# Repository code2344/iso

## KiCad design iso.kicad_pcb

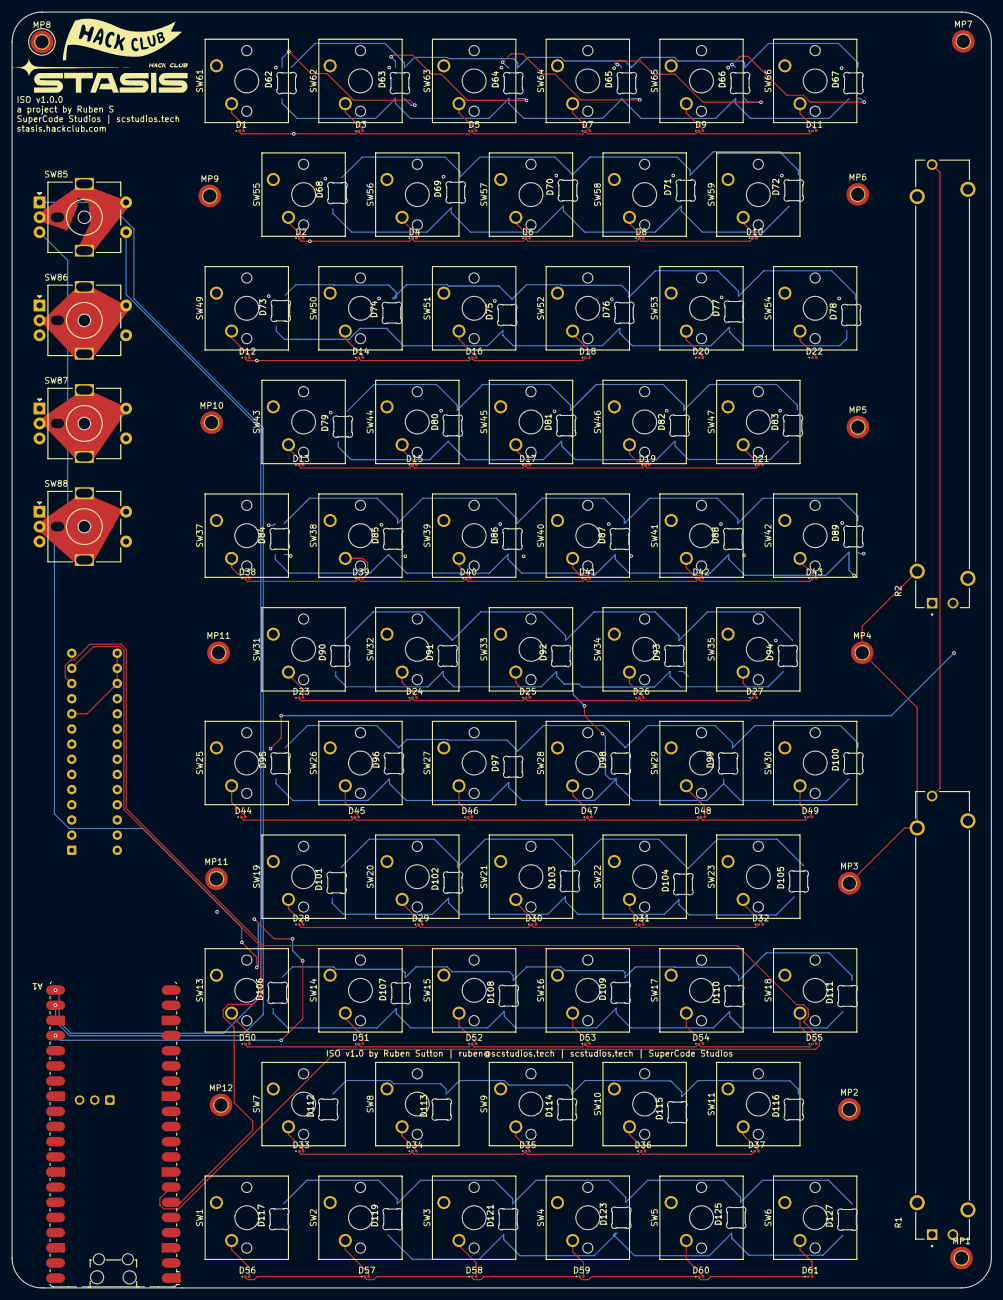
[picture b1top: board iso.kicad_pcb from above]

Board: 4 copper layers, 164.1 x 213.8 mm, 204 parts (1 on the bottom side), 158 nets.

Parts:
A1: RaspberryPi_Pico_W; RaspberryPi_Pico_W_SMD_HandSolder
D1, D2, D3, D4, D5, D6, D7, D8, D9, D10, D11, D12, D13, D14, D15, D16, D17, D18, D19, D20, D21, D22, D23, D24, D25, D26, D27, D28, D29, D30, D31, D32, D33, D34, D35, D36, D37, D38, D39, D40, D41, D42, D43, D44, D45, D46, D47, D48, D49, D50, D51, D52, D53, D54, D55, D56, D57, D58, D59, D60, D61: D_Small; D_0201_0603Metric
D62, D63, D64, D65, D66, D67, D68, D69, D70, D71, D72, D73, D74, D75, D76, D77, D78, D79, D80, D81, D82, D83, D84, D85, D86, D87, D88, D89, D90, D91, D92, D93, D94, D95, D96, D97, D98, D99, D100, D101, D102, D103, D104, D105, D106, D107, D108, D109, D110, D111, D112, D113, D114, D115, D116, D117, D119, D121, D123, D125, D127: SK6812; SK6812MINI-E_fixed
MP1, MP2, MP3, MP4, MP5, MP6, MP7, MP8, MP9, MP10, MP11, MP11#2, MP12: MountingHole_2.2mm_M2_DIN965_Pad_TopBottom
R1, R2: PTA6043-2015DPB103; TRIM_PTA6043-2015DPB103
SW1, SW2, SW3, SW4, SW5, SW6, SW7, SW8, SW9, SW10, SW11, SW13, SW14, SW15, SW16, SW17, SW18, SW19, SW20, SW21, SW22, SW23, SW25, SW26, SW27, SW28, SW29, SW30, SW31, SW32, SW33, SW34, SW35, SW37, SW38, SW39, SW40, SW41, SW42, SW43, SW44, SW45, SW46, SW47, SW49, SW50, SW51, SW52, SW53, SW54, SW55, SW56, SW57, SW58, SW59, SW61, SW62, SW63, SW64, SW65, SW66: SW_Push; SW_Cherry_MX_1.00u_PCB
SW85, SW86, SW87, SW88: RotaryEncoder_Switch_MP; RotaryEncoder_Alps_EC11E-Switch_Vertical_H20mm_MountingHoles
U1: MCP23017_SP; DIP-28_W7.62mm

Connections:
+3.3V: R1.3, R2.3
+5V: D62.3 (VDD), D63.3 (VDD), D64.3 (VDD), D65.3 (VDD), D66.3 (VDD), D67.3 (VDD), D68.3 (VDD), D69.3 (VDD), D70.3 (VDD), D71.3 (VDD), D72.3 (VDD), D73.3 (VDD), D74.3 (VDD), D75.3 (VDD), D76.3 (VDD), D77.3 (VDD), D78.3 (VDD), D79.3 (VDD), D80.3 (VDD), D81.3 (VDD), D82.3 (VDD), D83.3 (VDD), D84.3 (VDD), D85.3 (VDD), D86.3 (VDD), D87.3 (VDD), D88.3 (VDD), D89.3 (VDD), D90.3 (VDD), D91.3 (VDD), D92.3 (VDD), D93.3 (VDD), D94.3 (VDD), D95.3 (VDD), D96.3 (VDD), D97.3 (VDD), D98.3 (VDD), D99.3 (VDD), D100.3 (VDD), D101.3 (VDD), D102.3 (VDD), D103.3 (VDD), D104.3 (VDD), D105.3 (VDD), D106.3 (VDD), D107.3 (VDD), D108.3 (VDD), D109.3 (VDD), D110.3 (VDD), D111.3 (VDD), D112.3 (VDD), D113.3 (VDD), D114.3 (VDD), D115.3 (VDD), D116.3 (VDD), D117.3 (VDD), D119.3 (VDD), D121.3 (VDD), D123.3 (VDD), D125.3 (VDD), D127.3 (VDD)
/2A: A1.9 (GPIO6), SW86.A
/2S: A1.10 (GPIO7), SW86.S1
/3A: A1.11 (GPIO8), SW87.A
/3S: A1.12 (GPIO9), SW87.S1
/4A: A1.14 (GPIO10), SW88.A
/4S: A1.15 (GPIO11), SW88.S1
/ADC1: A1.32 (GPIO27_ADC1), R2.2
/ADC2: A1.34 (GPIO28_ADC2), R1.2
/LEDDIN: A1.16 (GPIO12), D62.2 (DIN)
/SCL: A1.7 (GPIO5), U1.12 (SCK)
/SDA: A1.6 (GPIO4), U1.13 (SDA)
/matrix/COL0: SW1.1, SW7.1, SW13.1, SW19.1, SW25.1, SW31.1, SW37.1, SW43.1, SW49.1, SW55.1, SW61.1, U1.5 (GPB4)
/matrix/COL1: SW2.1, SW8.1, SW14.1, SW20.1, SW26.1, SW32.1, SW38.1, SW44.1, SW50.1, SW56.1, SW62.1, U1.4 (GPB3)
/matrix/COL2: SW3.1, SW9.1, SW15.1, SW21.1, SW27.1, SW33.1, SW39.1, SW45.1, SW51.1, SW57.1, SW63.1, U1.3 (GPB2)
/matrix/COL3: SW4.1, SW10.1, SW16.1, SW22.1, SW28.1, SW34.1, SW40.1, SW46.1, SW52.1, SW58.1, SW64.1, U1.2 (GPB1)
/matrix/COL4: SW5.1, SW11.1, SW17.1, SW23.1, SW29.1, SW35.1, SW41.1, SW47.1, SW53.1, SW59.1, SW65.1, U1.1 (GPB0)
/matrix/COL5: A1.29 (GPIO22), SW6.1, SW18.1, SW30.1, SW42.1, SW54.1, SW66.1
/matrix/ROW0: D1.1 (K), D3.1 (K), D5.1 (K), D7.1 (K), D9.1 (K), D11.1 (K), U1.6 (GPB5)
/matrix/ROW1: D2.1 (K), D4.1 (K), D6.1 (K), D8.1 (K), D10.1 (K), U1.7 (GPB6)
/matrix/ROW2: D12.1 (K), D14.1 (K), D16.1 (K), D18.1 (K), D20.1 (K), D22.1 (K), U1.8 (GPB7)
/matrix/ROW3: D13.1 (K), D15.1 (K), D17.1 (K), D19.1 (K), D21.1 (K), U1.21 (GPA0)
/matrix/ROW4: D38.1 (K), D39.1 (K), D40.1 (K), D41.1 (K), D42.1 (K), D43.1 (K), U1.22 (GPA1)
/matrix/ROW5: D23.1 (K), D24.1 (K), D25.1 (K), D26.1 (K), D27.1 (K), U1.23 (GPA2)
/matrix/ROW6: D44.1 (K), D45.1 (K), D46.1 (K), D47.1 (K), D48.1 (K), D49.1 (K), U1.24 (GPA3)
/matrix/ROW7: D28.1 (K), D29.1 (K), D30.1 (K), D31.1 (K), D32.1 (K), U1.25 (GPA4)
/matrix/ROW8: D50.1 (K), D51.1 (K), D52.1 (K), D53.1 (K), D54.1 (K), D55.1 (K), U1.26 (GPA5)
/matrix/ROW9: D33.1 (K), D34.1 (K), D35.1 (K), D36.1 (K), D37.1 (K), U1.27 (GPA6)
/matrix/ROW10: D56.1 (K), D57.1 (K), D58.1 (K), D59.1 (K), D60.1 (K), D61.1 (K), U1.28 (GPA7)
GND: A1.3 (GND), A1.8 (GND), A1.13 (GND), A1.18 (GND), A1.23 (GND), A1.28 (GND), A1.38 (GND), D62.1 (VSS), D63.1 (VSS), D64.1 (VSS), D65.1 (VSS), D66.1 (VSS), D67.1 (VSS), D68.1 (VSS), D69.1 (VSS), D70.1 (VSS), D71.1 (VSS), D72.1 (VSS), D73.1 (VSS), D74.1 (VSS), D75.1 (VSS), D76.1 (VSS), D77.1 (VSS), D78.1 (VSS), D79.1 (VSS), D80.1 (VSS), D81.1 (VSS), D82.1 (VSS), D83.1 (VSS), D84.1 (VSS), D85.1 (VSS), D86.1 (VSS), D87.1 (VSS), D88.1 (VSS), D89.1 (VSS), D90.1 (VSS), D91.1 (VSS), D92.1 (VSS), D93.1 (VSS), D94.1 (VSS), D95.1 (VSS), D96.1 (VSS), D97.1 (VSS), D98.1 (VSS), D99.1 (VSS), D100.1 (VSS), D101.1 (VSS), D102.1 (VSS), D103.1 (VSS), D104.1 (VSS), D105.1 (VSS), D106.1 (VSS), D107.1 (VSS), D108.1 (VSS), D109.1 (VSS), D110.1 (VSS), D111.1 (VSS), D112.1 (VSS), D113.1 (VSS), D114.1 (VSS), D115.1 (VSS), D116.1 (VSS), D117.1 (VSS), D119.1 (VSS), D121.1 (VSS), D123.1 (VSS), D125.1 (VSS), D127.1 (VSS), R1.1, R2.1, SW85.C, SW85.MP, SW85.S2, SW86.C, SW86.MP, SW86.S2, SW87.C, SW87.MP, SW87.S2, SW88.C, SW88.MP, SW88.S2, U1.10 (VSS), U1.15 (A0), U1.16 (A1), U1.17 (A2)
unnamed: A1.21 (GPIO16), SW85.S1
unnamed: A1.22 (GPIO17), SW85.A
unnamed: A1.24 (GPIO18), SW85.B
unnamed: A1.25 (GPIO19), SW86.B
unnamed: A1.26 (GPIO20), SW87.B
unnamed: A1.27 (GPIO21), SW88.B
unnamed: D1.2 (A), SW61.2
unnamed: D2.2 (A), SW55.2
unnamed: D3.2 (A), SW62.2
unnamed: D4.2 (A), SW56.2
unnamed: D5.2 (A), SW63.2
unnamed: D6.2 (A), SW57.2
unnamed: D7.2 (A), SW64.2
unnamed: D8.2 (A), SW58.2
unnamed: D9.2 (A), SW65.2
unnamed: D10.2 (A), SW59.2
unnamed: D11.2 (A), SW66.2
unnamed: D12.2 (A), SW49.2
unnamed: D13.2 (A), SW43.2
unnamed: D14.2 (A), SW50.2
unnamed: D15.2 (A), SW44.2
unnamed: D16.2 (A), SW51.2
unnamed: D17.2 (A), SW45.2
unnamed: D18.2 (A), SW52.2
unnamed: D19.2 (A), SW46.2
unnamed: D20.2 (A), SW53.2
unnamed: D21.2 (A), SW47.2
unnamed: D22.2 (A), SW54.2
unnamed: D23.2 (A), SW31.2
unnamed: D24.2 (A), SW32.2
unnamed: D25.2 (A), SW33.2
unnamed: D26.2 (A), SW34.2
unnamed: D27.2 (A), SW35.2
unnamed: D28.2 (A), SW19.2
unnamed: D29.2 (A), SW20.2
unnamed: D30.2 (A), SW21.2
unnamed: D31.2 (A), SW22.2
unnamed: D32.2 (A), SW23.2
unnamed: D33.2 (A), SW7.2
unnamed: D34.2 (A), SW8.2
unnamed: D35.2 (A), SW9.2
unnamed: D36.2 (A), SW10.2
unnamed: D37.2 (A), SW11.2
unnamed: D38.2 (A), SW37.2
unnamed: D39.2 (A), SW38.2
unnamed: D40.2 (A), SW39.2
unnamed: D41.2 (A), SW40.2
unnamed: D42.2 (A), SW41.2
unnamed: D43.2 (A), SW42.2
unnamed: D44.2 (A), SW25.2
unnamed: D45.2 (A), SW26.2
unnamed: D46.2 (A), SW27.2
unnamed: D47.2 (A), SW28.2
unnamed: D48.2 (A), SW29.2
unnamed: D49.2 (A), SW30.2
unnamed: D50.2 (A), SW13.2
unnamed: D51.2 (A), SW14.2
unnamed: D52.2 (A), SW15.2
unnamed: D53.2 (A), SW16.2
unnamed: D54.2 (A), SW17.2
unnamed: D55.2 (A), SW18.2
unnamed: D56.2 (A), SW1.2
unnamed: D57.2 (A), SW2.2
unnamed: D58.2 (A), SW3.2
unnamed: D59.2 (A), SW4.2
unnamed: D60.2 (A), SW5.2
unnamed: D61.2 (A), SW6.2
unnamed: D62.4 (DOUT), D63.2 (DIN)
unnamed: D63.4 (DOUT), D64.2 (DIN)
unnamed: D64.4 (DOUT), D65.2 (DIN)
unnamed: D65.4 (DOUT), D66.2 (DIN)
unnamed: D66.4 (DOUT), D67.2 (DIN)
unnamed: D67.4 (DOUT), D68.2 (DIN)
unnamed: D68.4 (DOUT), D69.2 (DIN)
unnamed: D69.4 (DOUT), D70.2 (DIN)
unnamed: D70.4 (DOUT), D71.2 (DIN)
unnamed: D71.4 (DOUT), D72.2 (DIN)
unnamed: D72.4 (DOUT), D73.2 (DIN)
unnamed: D73.4 (DOUT), D75.2 (DIN)
unnamed: D74.2 (DIN), D83.4 (DOUT)
unnamed: D74.4 (DOUT), D76.2 (DIN)
unnamed: D75.4 (DOUT), D77.2 (DIN)
unnamed: D76.4 (DOUT), D78.2 (DIN)
unnamed: D77.4 (DOUT), D79.2 (DIN)
unnamed: D78.4 (DOUT), D80.2 (DIN)
unnamed: D79.4 (DOUT), D81.2 (DIN)
unnamed: D80.4 (DOUT), D82.2 (DIN)
unnamed: D81.4 (DOUT), D83.2 (DIN)
unnamed: D82.4 (DOUT), D84.2 (DIN)
unnamed: D84.4 (DOUT), D86.2 (DIN)
unnamed: D85.2 (DIN), D94.4 (DOUT)
unnamed: D85.4 (DOUT), D87.2 (DIN)
unnamed: D86.4 (DOUT), D88.2 (DIN)
unnamed: D87.4 (DOUT), D89.2 (DIN)
unnamed: D88.4 (DOUT), D90.2 (DIN)
unnamed: D89.4 (DOUT), D91.2 (DIN)
unnamed: D90.4 (DOUT), D92.2 (DIN)
unnamed: D91.4 (DOUT), D93.2 (DIN)
unnamed: D92.4 (DOUT), D94.2 (DIN)
unnamed: D93.4 (DOUT), D95.2 (DIN)
unnamed: D95.4 (DOUT), D97.2 (DIN)
unnamed: D96.4 (DOUT), D98.2 (DIN)
unnamed: D97.4 (DOUT), D99.2 (DIN)
unnamed: D98.4 (DOUT), D100.2 (DIN)
unnamed: D100.4 (DOUT), D102.2 (DIN)
unnamed: D99.4 (DOUT), D101.2 (DIN)
unnamed: D101.4 (DOUT), D103.2 (DIN)
unnamed: D102.4 (DOUT), D104.2 (DIN)
unnamed: D103.4 (DOUT), D105.2 (DIN)
unnamed: D104.4 (DOUT), D106.2 (DIN)
unnamed: D96.2 (DIN), D105.4 (DOUT)
unnamed: D106.4 (DOUT), D108.2 (DIN)
unnamed: D107.2 (DIN), D116.4 (DOUT)
unnamed: D107.4 (DOUT), D109.2 (DIN)
unnamed: D108.4 (DOUT), D110.2 (DIN)
unnamed: D109.4 (DOUT), D111.2 (DIN)
unnamed: D110.4 (DOUT), D112.2 (DIN)
unnamed: D111.4 (DOUT), D113.2 (DIN)
unnamed: D112.4 (DOUT), D114.2 (DIN)
unnamed: D113.4 (DOUT), D115.2 (DIN)
unnamed: D114.4 (DOUT), D116.2 (DIN)
unnamed: D115.4 (DOUT), D117.2 (DIN)
unnamed: D117.4 (DOUT), D119.2 (DIN)
unnamed: D119.4 (DOUT), D121.2 (DIN)
unnamed: D121.4 (DOUT), D123.2 (DIN)
unnamed: D123.4 (DOUT), D125.2 (DIN)
unnamed: D125.4 (DOUT), D127.2 (DIN)
